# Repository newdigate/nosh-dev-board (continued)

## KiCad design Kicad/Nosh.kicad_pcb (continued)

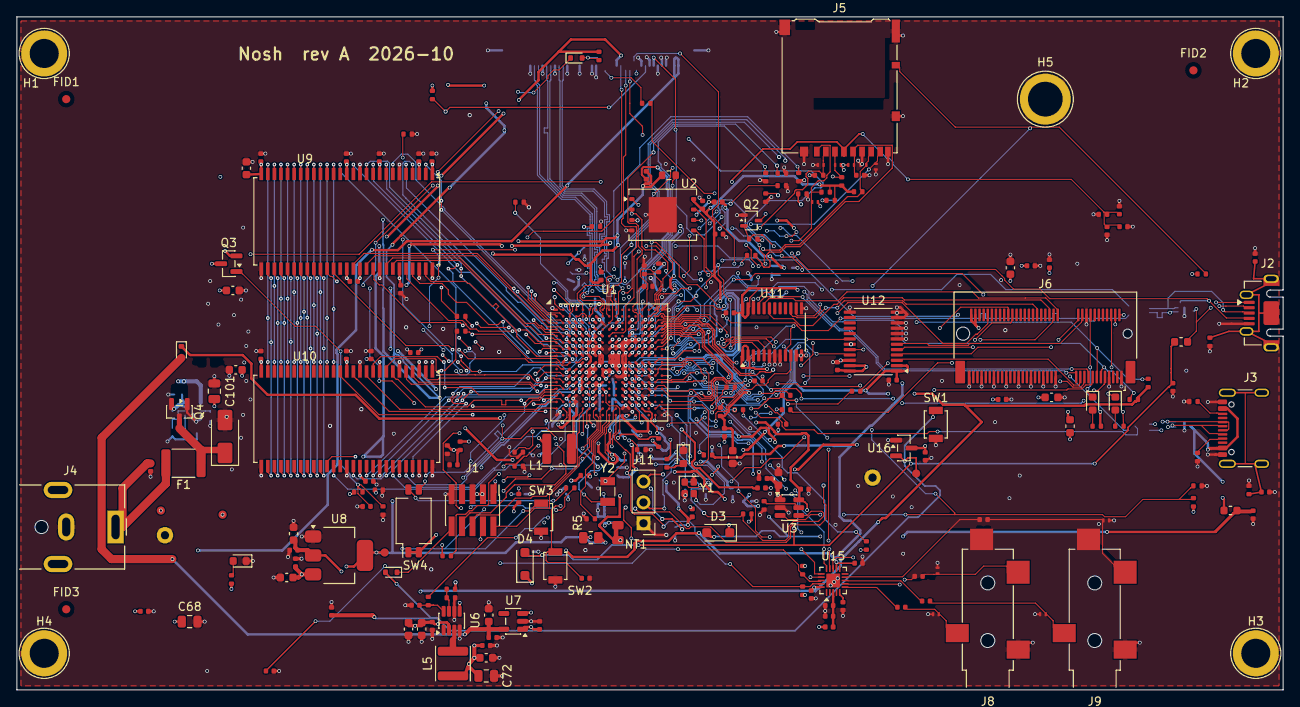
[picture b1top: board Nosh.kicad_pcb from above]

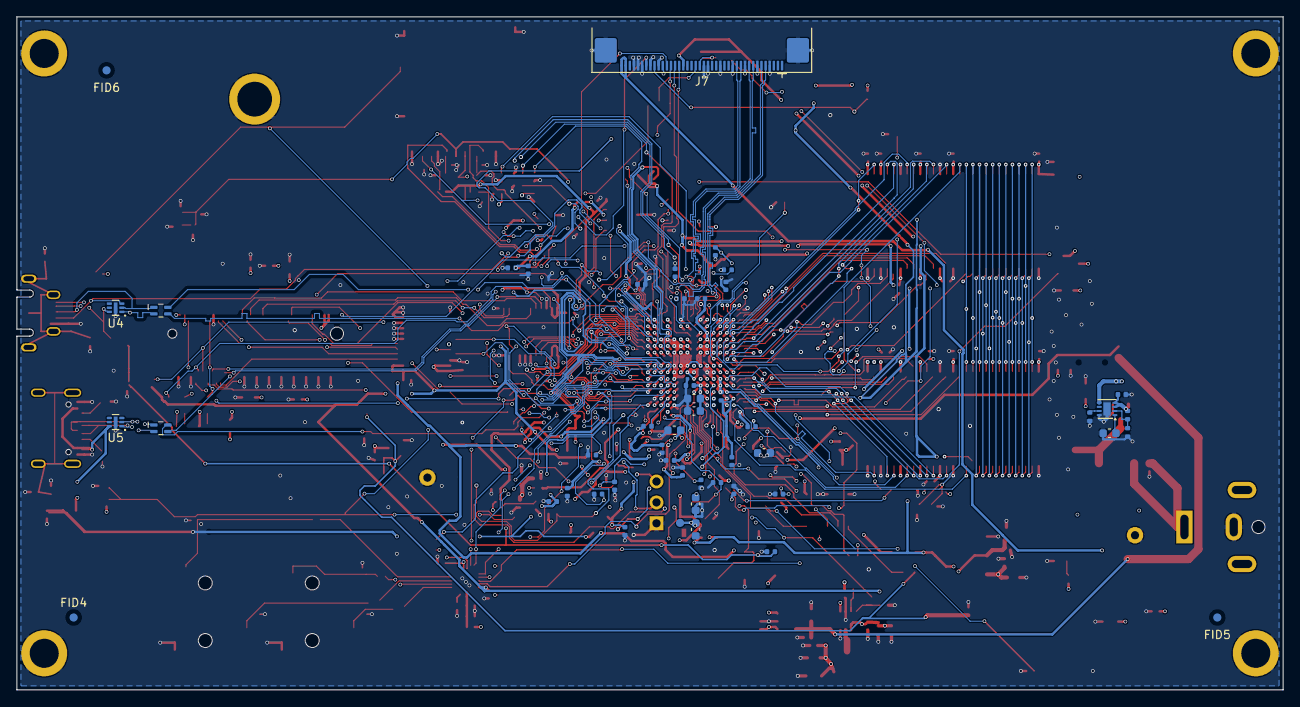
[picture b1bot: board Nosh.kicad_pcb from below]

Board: 6 copper layers, 153.9 x 81.8 mm, 294 parts (75 on the bottom side), 238 nets.

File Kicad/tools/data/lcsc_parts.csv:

LCSC,MPN,Value,Footprint,Qty,Refs
C1525,CL05B104KO5NNNC,100nF,C_0402_1005Metric_JLC,51,C56 C29 C9 C57 C25 C33 C3 C12 C21 C46 C22 C55 C146 C59 C63 C74 C82 C70 C69 C84 C77 C80 C148 C88 C93 C85 C90 C95 C86 C98 C91 C96 C99 C89 C94 C87 C97 C108 C105 C109 C111 C113 C106 C114 C107 C112 C119 C129 C130 C131 C127
C25741,0402WGF1003TCE,100k,R_0402_1005Metric_JLC,18,R95 R92 R91 R93 R90 R99 R103 R97 R102 R98 R100 R96 R101 R94 R19 R24 R105 R55
C25744,0402WGF1002TCE,10k,R_0402_1005Metric_JLC,17,R10 R14 R13 R20(DNP) R18 R28 R43 R46 R49 R44 R54 R57 R53 R59 R108 R109 R73 R66
C52923,CL05A105KA5NQNC,1uF,C_0402_1005Metric_ViP,18,C19 C8 C1 C20 C11 C50 C51 C48 C49 C47 C52 C58 C78 C117 C133 C141 C142 C132
C12530,CL05A225MQ5NSNC,2.2uF,C_0402_1005Metric_JLC,15,C14 C7 C2 C32 C13 C28 C44 C39 C36 C42 C34 C35 C38 C40 C118
C23733,CL05A475MP5NRNC,4.7uF,C_0402_1005Metric_JLC,14,C6 C10 C18 C5 C24 C17 C16 C43 C37 C41 C64 C66 C65 C128
C17168,0402WGF0000TCE,0R,R_0402_1005Metric_JLC,8,R8 R7 R42 R41 R56 R67(DNP) R85(DNP) R83 R81 R82 R84(DNP)
C19702,CL10A106KP8NNNC,10uF,C_0603_1608Metric,11,C27 C31 C60 C62 C83 C73 C75 C76 C81 C104 C103
C85812,BLM15AG121SN1D,120R,L_0402_1005Metric,7,FB2 FB1 FB3 FB4 FB5 FB6 FB11
C11702,0402WGF1001TCE,1k,R_0402_1005Metric_JLC,6,R89 R104 R52 R51 R60 R58
C436349,TPD1E05U06DPYR,TPD1E05U06,ESD_X1SON-2_0.6x1mm_JLC,6,D13 D14 D15 D16 D17 D18
C16772,CL05B224KO5NNNC,220nF,C_0402_1005Metric_JLC,4,C4 C45 C71 C116
C19666,CL10A475KO8NNNC,4.7uF,C_0603_1608Metric,4,C79 C100 C92 C102
C2286,KT-0603R,RED,LED_0603_1608Metric,4,D10 D11 D6 D7
C25900,0402WGF4701TCE,4.7k,R_0402_1005Metric_JLC,3,R3(DNP) R2 R11 R12
C48260,TPD1E10B06DPYR,TPD1E10B06,ESD_X1SON-2_0.6x1mm_JLC,4,D19 D20 D21 D22
C59461,CL10A226MQ8NRNC,22uF,C_0603_1608Metric,4,C15 C26 C30 C23
C145179,RB521S30T1G,RB521S30,D_SOD-523,3,D1 D5 D9
C231329,B3U-1000P,RESET,SW_SPST_B3U-1000P,3,SW1 SW3 SW2
C45783,CL21A226MAQNNNE,22uF,C_0805_2012Metric,3,C72 C68 C101
C107022,CC0402KRX7R9BB152,1.5nF,C_0402_1005Metric_JLC,2,C67 C61
C1349997,AS4C32M16SC-7TIN,AS4C32M16SC-7TIN,TSOP-II-54_22.2x10.16mm_P0.8mm,2,U10 U9
C14709,BLM18PG121SN1D,120R,L_0603_1608Metric,2,FB7 FB10
C20182907,SJ-3524-SMT-TR,LINE OUT,Jack_3.5mm_CUI_SJ-3524-SMT_Horizontal_JLC,2,J8 J9
C223608,MBR120VLSFT1G,MBR120VLSFT1G,D_SOD-123F,2,D3 D4
C25076,0402WGF1000TCE,100R,R_0402_1005Metric_JLC,2,R16 R27
C25100,0402WGF270JTCE,27R,R_0402_1005Metric_JLC,2,R50 R47
C25879,0402WGF2201TCE,2.2k,R_0402_1005Metric_JLC,2,R74 R75
C25905,0402WGF5101TCE,5.1k,R_0402_1005Metric_JLC,2,R25 R26
C3034,IRLML6401TRPBF,IRLML6401,SOT-23,2,Q4 Q3
C325453,CC0402BRNPO9BN4R7,4.7pF,C_0402_1005Metric_JLC,2,C53 C54
C32949,CL05C100JB5NNNC,10pF,C_0402_1005Metric_JLC,2,C143 C144
C465742,SN74AVC8T245PWR,74AVC8T245PW,TSSOP-24_4.4x7.8mm_P0.65mm,2,U12 U11
C80529,DLW21HN900SQ2L,DLW21HN900SQ2L,L_CommonModeChoke_Murata_DLW21,2,L3 L4
C842842,RCLAMP0854P.TCT,RClamp0854P,slp1616p6,2,U5 U4
C1020237,MIMXRT1176DVMAA,MIMXRT1176DVMAA,MAPBGA-289_14x14mm_Layout17x17_P0.8mm,1,U1
C113315,2SK3018T106,2SK3018,SOT-323_SC-70,1,Q2
C114218,DM3AT-SF-PEJM5,microSD,microSD_HC_Hirose_DM3AT-SF-PEJM5_JLC,1,J5
C132016,TLV803SDBZR,TLV803S,SOT-23,1,U16
C136001,47590-0001,USB2 micro-AB,USB_Micro-AB_Molex_47590-0001_JLC,1,J2
C150517,20021121-00010C4LF,SWD,PinHeader_2x05_P1.27mm_Vertical_SMD,1,J1
C1545,0402CG100J500NT,10pF,C_0402_1005Metric_JLC,0,C145(DNP)
C1549,0402CG180J500NT,18pF,C_0402_1005Metric_JLC,0,C115(DNP)
C1613,CL10B332KB8NNNC,3.3nF,C_0603_1608Metric,1,C147
C17477,0805W8F0000T5E,0R,R_0805_2012Metric,0,R5(DNP)
C21189,0603WAF0000T5E,0R,R_0603_1608Metric,1,R40
C2155674,TPS259531DSGR,TPS259531,Texas_DSG0008A_WSON-8-1EP_2x2mm_P0.5mm_EP0.9x1.6mm,1,U17
C223993,SMAJ6.0A,SMAJ6.0A,D_SMA,1,D12
C22434582,PJ-063AH,DC 5V IN,BarrelJack_CUI_PJ-063AH_Horizontal_JLC,1,J4
C25126,0402WGF5600TCE,560R,R_0402_1005Metric_JLC,1,R107
C25760,0402WGF1803TCE,180k,R_0402_1005Metric_JLC,1,R29
C25768,0402WGF2202TCE,22k,R_0402_1005Metric_JLC,1,R23
C25792,0402WGF4702TCE,47k,R_0402_1005Metric_JLC,1,R106
C25893,0402WGF4022TCE,40.2k,R_0402_1005Metric_JLC,1,R30
C2649308,742792641,300R,L_0603_1608Metric,1,FB8
C2651833,SGTL5000XNLA3R2,SGTL5000XNLA3R2,QFN-20-1EP_3x3mm_P0.4mm_EP1.65x1.65mm,1,U15
C2892380,SMD1812P300SLR/24,3A,Fuse_1812_4532Metric,1,F1
C2909347,FRC0402F3002TS,30k,R_0402_1005Metric_JLC,1,R1
C2937625,PZ254V-11-03P,DEBUG UART,PinHeader_1x03_P2.54mm_Vertical,1,J11
C2977809,2199230-4,M.2 Key E (IW416 / MAYA-W1),M2_KeyE_67pin_RA,1,J6
C3293142,DSHP02TSGER,BOOT_MODE,SW_DIP_SPSTx02_Slide_KingTek_DSHP02TS_W7.62mm_P1.27mm,1,SW4
C43427,MP2143DJ-LF-Z,MP2143DJ,TSOT-23-8,1,U6
C48615,Q13FC13500002,32.768kHz,Crystal_SMD_3215-2Pin_3.2x1.5mm_JLC,1,Y2
C51118,AP2112K-3.3TRG1,AP2112K-3.3,SOT-23-5,1,U7
C5184243,USB4105-GF-A-120,USB1 USB-C,USB_C_Receptacle_GCT_USB4105-xx-A_16P_TopMnt_Horizontal_JLC,1,J3
C5250251,XRCGB24M000F2P91R0,24MHz,Crystal_SMD_2016-4Pin_2.0x1.6mm,1,Y1
C5301776,SMTSOM2.520BTR,M2.5 nut 2mm,SMTSO_M2.5_Hole4.22mm_Pad6.2mm,1,H5
C55266,TPS2553DBVR,TPS2553DBVR,SOT-23-6,1,U3
C6264899,68714014022,MIPI LCD FPC (RK055HDMIPI4MA0),FPC40_0p5_Wuerth_68714014022,1,J7
C6364800,ANR4020T4R7M,4.7uH,L_APV_ANR4020,1,L1
C7389628,W25Q512JVEIQ,W25Q512JVEIQ,WSON-8-1EP_8x6mm_P1.27mm_EP3.4x4.3mm,1,U2
C80105,TLV1117LV18DCYR,TLV1117LV-18,SOT-223-3_TabPin2,1,U8
C91254,SWPA4020S1R0NT,1uH 3A,L_APV_ANR4020,1,L5

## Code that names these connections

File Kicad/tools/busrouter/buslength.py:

"""Per-pin flight lengths of the SDRAM bus: shortest copper path from the MCU ball to each chip pin.
usage: buslength.py board.kicad_pcb [via_mm]        via_mm: length counted per via passed (default 0.8)
Tracks are split wherever another item's end lands on them; vias join all layers; pads join what lies on them.
Clock: SEMC_CLK from J3 to R41/R42 pad 1, plus U9_CLK / U10_CLK from pad 2 to pin 38 (+1 mm for the resistor).
Reports each pin against the clock length at the same chip.
"""
import sys, re, math, heapq, collections, pcbnew
from pcbnew import ToMM
b = pcbnew.LoadBoard(sys.argv[1]); VIA_MM = float(sys.argv[2]) if len(sys.argv) > 2 else 0.8
SD = re.compile(r'^(SEMC_|U9_CLK$|U10_CLK$)')
Q = lambda v: round(ToMM(v) * 1000)                    # micrometre keys
items = collections.defaultdict(lambda: {'trk': [], 'via': [], 'pad': []})
for t in b.GetTracks():
    n = t.GetNetname()
    if not SD.match(n): continue
    if t.Type() == pcbnew.PCB_VIA_T: items[n]['via'].append((Q(t.GetPosition().x), Q(t.GetPosition().y), round(ToMM(t.GetWidth(pcbnew.F_Cu)) * 500)))
    else: items[n]['trk'].append((t.GetLayer(), Q(t.GetStart().x), Q(t.GetStart().y), Q(t.GetEnd().x), Q(t.GetEnd().y), round(ToMM(t.GetWidth()) * 500)))
for f in b.GetFootprints():
    for p in f.Pads():
        n = p.GetNetname()
        if SD.match(n): items[n]['pad'].append((f.GetReference(), p.GetNumber(), p, {l for l in (pcbnew.F_Cu, pcbnew.B_Cu, b.GetLayerID('SIG')) if p.IsOnLayer(l)}))

def lengths(net, start_pad):
    it = items[net]; adj = collections.defaultdict(list)
    def edge(a, c, w): adj[a].append((c, w)); adj[c].append((a, w))
    pts = collections.defaultdict(set)                  # layer -> endpoints
    for l, x0, y0, x1, y1, hw in it['trk']: pts[l].add((x0, y0)); pts[l].add((x1, y1))
    for x, y, r in it['via']:
        for l in pts: pts[l].add((x, y))
    for l, x0, y0, x1, y1, hw in it['trk']:               # split each track at points lying on it
        dx, dy = x1 - x0, y1 - y0; L2 = dx * dx + dy * dy; on = [(0.0, (x0, y0)), (1.0, (x1, y1))]
        for (px, py) in pts[l]:
            if L2 == 0: continue
            t = ((px - x0) * dx + (py - y0) * dy) / L2
            if 0 < t < 1 and abs((px - x0) * dy - (py - y0) * dx) / math.sqrt(L2) <= hw: on.append((t, (px, py)))
        on.sort()
        for (ta, pa), (tb, pb) in zip(on, on[1:]): edge((l, pa), (l, pb), math.hypot(pb[0] - pa[0], pb[1] - pa[1]) / 1000)
    for x, y, r in it['via']:                            # via: a hub joined to every layer node within its pad
        hub = ('via', x, y)
        for l in pts:
            for (px, py) in pts[l]:
                if math.hypot(px - x, py - y) <= r: edge(hub, (l, (px, py)), VIA_MM / 2)
    for ref, num, p, lays in it['pad']:                  # pad: a hub joined to every node on it
        hub = ('pad', ref, num)
        for l in lays:
            for (px, py) in pts.get(l, ()):
                if p.HitTest(pcbnew.VECTOR2I(px * 1000, py * 1000)):
                    c = p.GetPosition(); edge(hub, (l, (px, py)), math.hypot(px - Q(c.x), py - Q(c.y)) / 1000)
        for x, y, r in it['via']:
            if any(p.IsOnLayer(l) for l in lays) and p.HitTest(pcbnew.VECTOR2I(x * 1000, y * 1000)): edge(hub, ('via', x, y), 0.0)
    src = ('pad',) + start_pad; dist = {src: 0.0}; pq = [(0.0, 0, src)]; tie = 0
    while pq:
        d, _, u = heapq.heappop(pq)
        if d > dist.get(u, 1e18): continue
        for v, w in adj[u]:
            if d + w < dist.get(v, 1e18): dist[v] = d + w; tie += 1; heapq.heappush(pq, (d + w, tie, v))
    return {(k[1], k[2]): v for k, v in dist.items() if k[0] == 'pad'}

u1_ball = {}
for n, it in items.items():
    for ref, num, p, lays in it['pad']:
        if ref == 'U1': u1_ball[n] = (ref, num)
clk = {}
dc = lengths('SEMC_CLK', u1_ball['SEMC_CLK'])
for chip, r, net in (('U9', 'R41', 'U9_CLK'), ('U10', 'R42', 'U10_CLK')):
    a = dc.get((r, '1')); bb = lengths(net, (r, '2')).get((chip, '38'))
    clk[chip] = None if a is None or bb is None else a + 1.0 + bb
print('clock to pin 38: U9 %s mm, U10 %s mm' % tuple('%.1f' % clk[c] if clk[c] else 'OPEN' for c in ('U9', 'U10')))
rows = []
for n in sorted(items, key=lambda s: (re.sub(r'\d+', '', s), int(re.search(r'(\d+)$', s).group(1)) if re.search(r'\d$', s) else 0)):
    if n in ('SEMC_CLK', 'U9_CLK', 'U10_CLK', 'SEMC_DQS') or n not in u1_ball: continue
    d = lengths(n, u1_ball[n])
    for ref, num, p, lays in items[n]['pad']:
        if ref not in ('U9', 'U10'): continue
        L = d.get((ref, num)); rows.append((n, ref, num, L, None if L is None or clk[ref] is None else L - clk[ref]))
for n, ref, num, L, dlt in rows:
    print('  %-10s %-3s pin %-2s %s' % (n, ref, num, 'OPEN' if L is None else '%5.1f mm  vs clock %+6.1f' % (L, dlt)))
ok = [r for r in rows if r[3] is not None]
if ok:
    for chip in ('U9', 'U10'):
        ds = [r[4] for r in ok if r[1] == chip and r[4] is not None]
        if ds: print('%s: %d pins, vs clock %+.1f .. %+.1f mm, longest pin %.1f mm' % (chip, len(ds), min(ds), max(ds), max(r[3] for r in ok if r[1] == chip)))
print('open pins:', [(r[0], r[1], r[2]) for r in rows if r[3] is None])
# ---- summary for scripts: per chip, the signal span and the clock length that would centre it
import json
summary = {'clock': clk, 'pins': [(r[0], r[1], r[2], r[3]) for r in rows], 'chips': {}}
for chip in ('U9', 'U10'):
    ls = [r[3] for r in rows if r[1] == chip and r[3] is not None]
    if ls: summary['chips'][chip] = {'min': min(ls), 'max': max(ls), 'half_span': (max(ls) - min(ls)) / 2, 'centre': (max(ls) + min(ls)) / 2}
summary['score'] = max(c['half_span'] for c in summary['chips'].values()) if summary['chips'] else 1e9
print('SPAN U9 %.1f..%.1f  U10 %.1f..%.1f  worst half-span %.1f mm' % (summary['chips']['U9']['min'], summary['chips']['U9']['max'], summary['chips']['U10']['min'], summary['chips']['U10']['max'], summary['score']))
if len(sys.argv) > 3: json.dump(summary, open(sys.argv[3], 'w'))
